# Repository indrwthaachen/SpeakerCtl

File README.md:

SPEAKERCTL
========

SpeakerCtl can be used to control NuPro(R) Speakers by IR and optical feedback.
It allows to set the volume from within Matlab or via a tray applet.
Also it can detect when the speaker hits the maximum output volume limit during playback.

PCBs
-------------------------
The file nuproRemote.brd/sch contains the main PCB , which is in Eagle format.
lcdInterface.brd/sch is a separate circuit board that is needed for I2C communication with the LCD.
PartsList.txt contains a list of all components that are necessary in order to assemble the PCBs.

uC Code
-------------------------------
The uC code can be compiled and run on Teensy 3.1 microcontroller boards.

Enclosure 
------------
The enclosure is made up of three parts:
* top.stl
* middle.stl
* bottom.stl

which can be easily 3D printed on any consumer-grade 3D Printer.
After printing these parts must be stacked/glued together. 

TrayTask 
------------
A Python script that connects via Bluetooth with multiple SPEAKERCTL boards and allows to control them.
It provides a TCP/IP interface for external programs but also contains a simple GUI for direct control by the user. 

Matlab 
------------
Matlab code that communicates over TCP/IP with the TrayTask process.

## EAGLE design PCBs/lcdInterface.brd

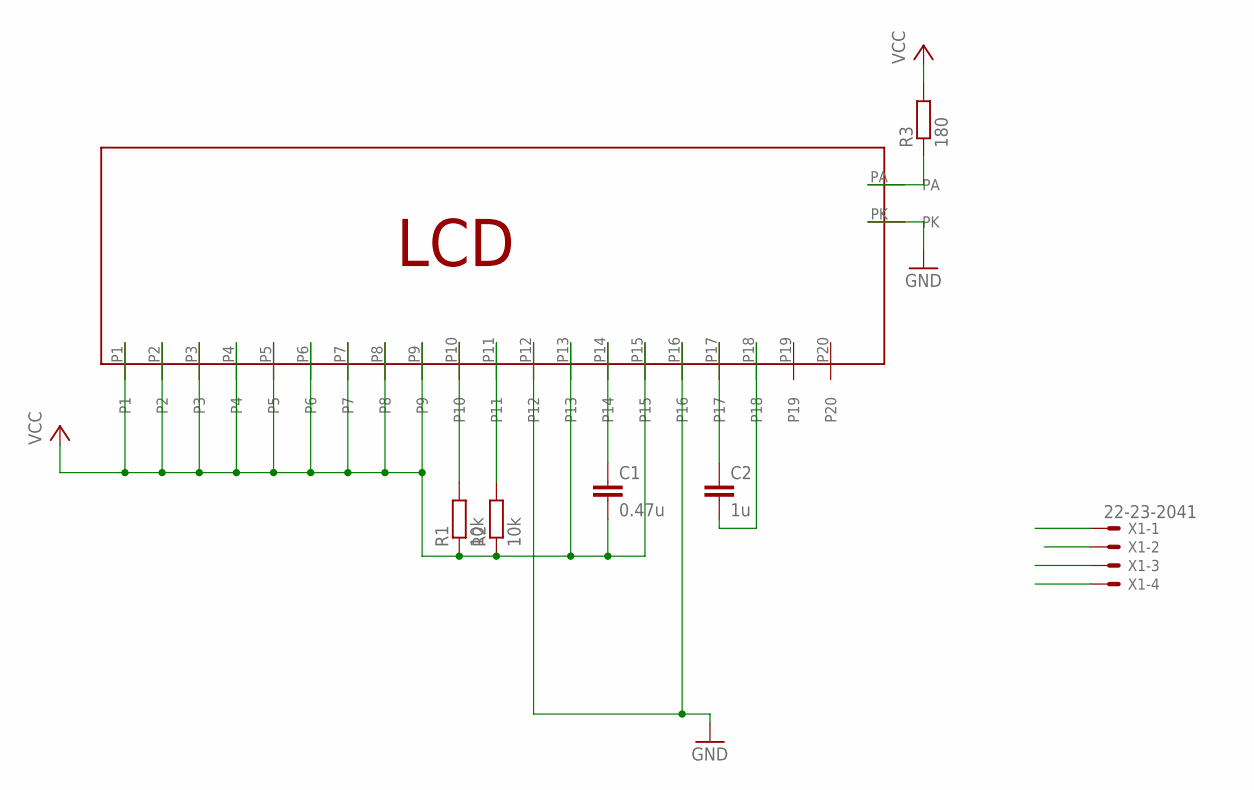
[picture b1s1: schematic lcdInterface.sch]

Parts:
C1: 0.47u; C050-055X075
C2: 1u; C050-030X075
R1, R2: 10k; 0207/10
R3: 180; 0207/10
U$1: GE-01602F; GE01602F
X1: 22-23-2041

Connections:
GND: U$1.P12, U$1.P16, U$1.PK, X1.4
unnamed: R3.1, U$1.PA
unnamed: C1.1, U$1.P14
unnamed: C2.1, U$1.P17
unnamed: C2.2, U$1.P18
SCL: R1.2, U$1.P10, X1.1
SDA: R2.2, U$1.P11, X1.2
VCC: C1.2, R1.1, R2.1, R3.2, U$1.P1, U$1.P2, U$1.P3, U$1.P4, U$1.P5, U$1.P6, U$1.P7, U$1.P8, U$1.P9, U$1.P13, U$1.P15, X1.3

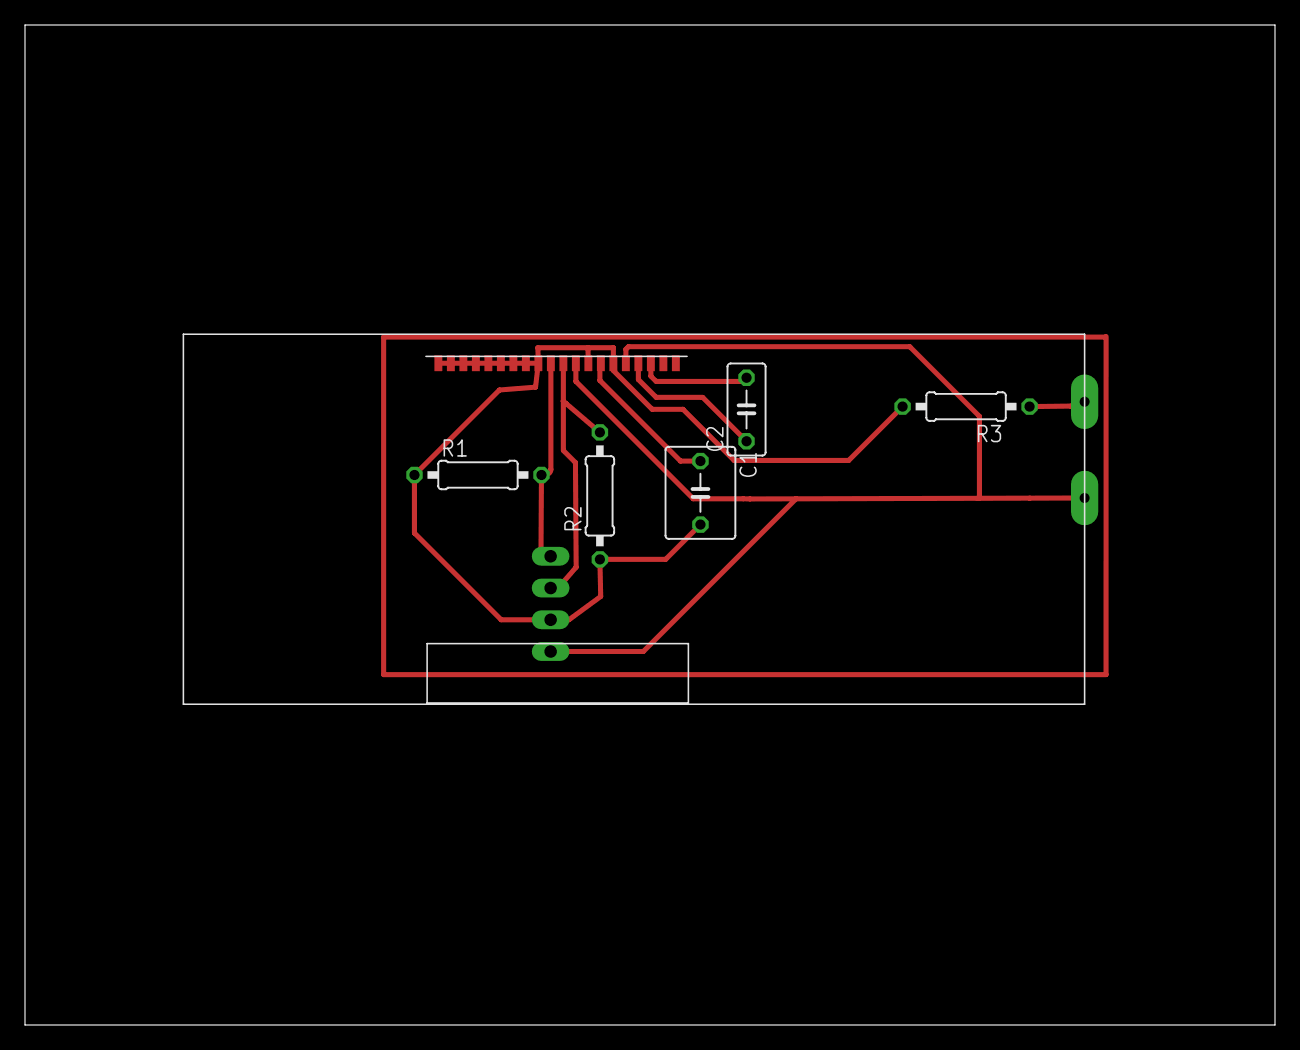
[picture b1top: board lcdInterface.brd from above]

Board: 2 copper layers, 100.0 x 80.0 mm, 7 parts (1 on the bottom side), 8 nets.

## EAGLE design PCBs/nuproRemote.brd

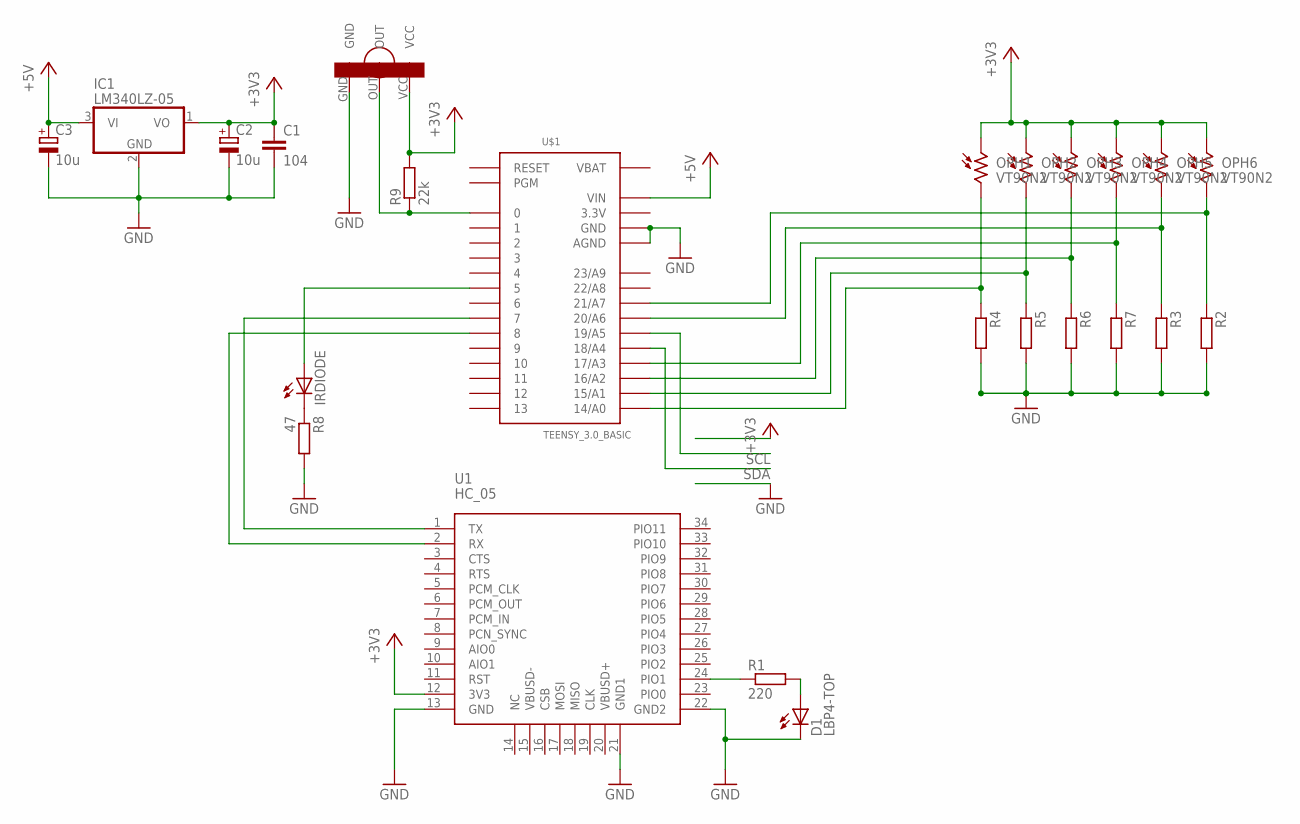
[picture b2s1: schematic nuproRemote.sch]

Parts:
C1: 104; C1206
C2, C3: 10u; C/6032-28R
D1: LBP4-TOP; LED3MM
IC1: LM340LZ-05; TO92
IRDIODE: LEDCHIP-LED0805; CHIP-LED0805
OPH1, OPH2, OPH3, OPH4, OPH5, OPH6: VT90N2; VT900
R1: 220; 0309/10
R2, R3, R4, R5, R6, R7: R-EU_0309/10; 0309/10
R8: 47; 0309/10
R9: 22k; 0309/10
U1: HC_05; BLUETOOTH_SMD
U$1: TEENSY_3.0_BASIC
U$2: OS-1838

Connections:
3.3V: U$1.3.3V, U$1.3.3V1 (3.3V)
+3V3: C1.1, C2.+, IC1.1 (VO), OPH1.1, OPH2.1, OPH3.1, OPH4.1, OPH5.1, OPH6.1, R9.2, U1.12 (3V3), U$2.VCC
+5V: C3.+, IC1.3 (VI), U$1.VIN
GND: C1.2, C2.-, C3.-, D1.K (C), IC1.2 (GND), R2.2, R3.2, R4.2, R5.2, R6.2, R7.2, R8.2, U1.13 (GND), U1.21 (GND1), U1.22 (GND2), U$1.AGND, U$1.GND, U$1.GND1 (GND), U$2.GND
unnamed: U1.2 (RX), U$1.8
unnamed: U1.1 (TX), U$1.7
unnamed: D1.A, R1.2
unnamed: IRDIODE.A, U$1.5
unnamed: R1.1, U1.24 (PIO1)
unnamed: OPH6.2, R2.1, U$1.21/A7
unnamed: OPH5.2, R3.1, U$1.20/A6
unnamed: IRDIODE.C, R8.1
unnamed: OPH1.2, R4.1, U$1.14/A0
unnamed: OPH2.2, R5.1, U$1.15/A1
unnamed: OPH3.2, R6.1, U$1.16/A2
unnamed: OPH4.2, R7.1, U$1.17/A3
unnamed: R9.1, U$1.0, U$2.OUT
SCL: U$1.19/A5
SDA: U$1.18/A4
VBAT: U$1.VBAT

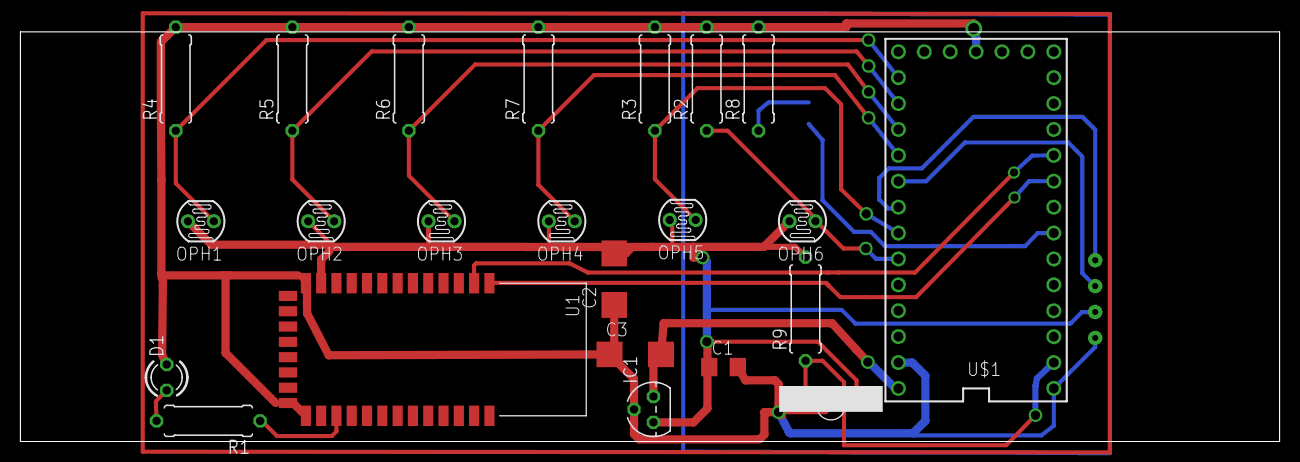
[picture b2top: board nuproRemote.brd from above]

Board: 2 copper layers, 123.5 x 40.2 mm, 24 parts (1 on the bottom side), 17 nets.

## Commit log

2015-01-16 added scan mode, increased switching delay, corrected naming
2015-01-16 added TrayTask code
2015-01-16 added Matlab code
